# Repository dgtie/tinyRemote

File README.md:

# This project is obsolete
- please click [new tiny IR remote](https://github.com/dgtie/tinyRemote1/tree/main)

# tinyRemote
An infrared remote control with attiny414\
powered by 2 x AAA

## Keys
```
              ____
vol- (99)    |o  o| ch-  (77)
vol+ (32)    |o  o| ch+  (31)
shift(power) |o  o| input(mute)
             |____|
              UUUU

Hit SHIFT and indicator will turn on. Then hit a button while indicator is on.

It shall work for SHARP, LG and TOSHIBA.
It shall also work for SONY, PHILIPS and SAMSUNG. (but not yet verified)
```
## Connecting to PC

```
              ____
             |o  o| GND
      [UART] |o  o| 3V3
         GND |o  o| [UPDI]
         3V3 |____|
              UUUU
```
Connect tinyRemote to PC using a USB2TTL module via UPDI port or UART port. UPDI port is for programming attiny414. I am using [pyupdi](https://github.com/mraardvark/pyupdi).\
UART port is used for reading infrared code. There is an infrared transistor near the LED indicator. Point your remote controller CLOSE to it. To enter reading mode:
1. remove batteries
2. power up tinyRemote via UART port
3. IF SUCCESS, indicator will turn on. (It is a minor bug! Upon startup, Rx pin is checked. If it is high, enter reading mode.)

Baud rate is 115200. PC will receive BINARIES from tinyRemote representing the durations of marks and spaces. ZERO means break. The timing unit is 4.8 us.\
b2str.cpp is to convert the binaries to readable text string. The output will be durations in us.\
Decoding is done by PC (decode.cpp)\
pronto.cpp converts pronto hex to durations stream that to be decoded by decode.cpp
## Schematic

https://user-images.githubusercontent.com/42087847/192790861-0ea7e591-97eb-486d-b9d1-ebd6bcc5e6a8.mp4

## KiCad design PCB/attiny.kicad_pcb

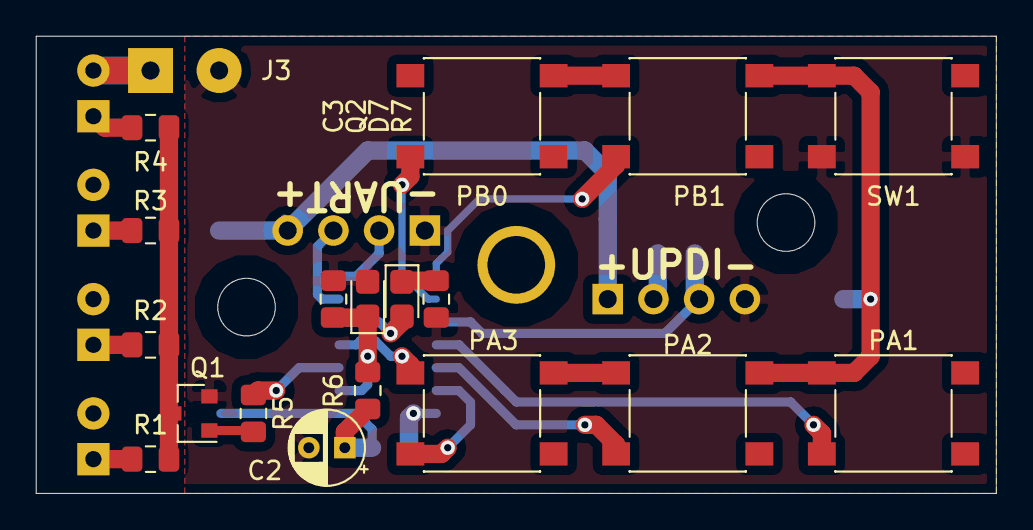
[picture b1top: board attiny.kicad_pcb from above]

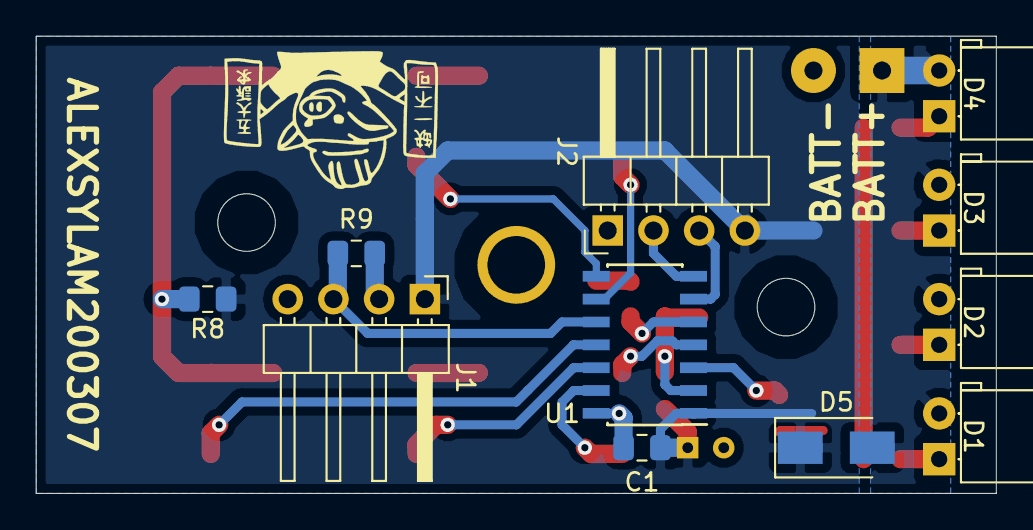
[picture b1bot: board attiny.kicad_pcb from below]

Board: 2 copper layers, 53.3 x 25.4 mm, 30 parts (11 on the bottom side), 23 nets.

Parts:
C1: 0u1; C_0805_2012Metric_Pad1.15x1.40mm_HandSolder
C2: 47u; CP_Radial_D4.0mm_P2.00mm
C3: 1n; C_0805_2012Metric_Pad1.15x1.40mm_HandSolder
D1, D2, D3, D4: LED; LED_D5.0mm_Horizontal_O1.27mm_Z3.0mm
D5: B120-E3; D_SMA
D7: LED; LED_0805_2012Metric_Castellated
J1, J2: Conn_01x04; PinHeader_1x04_P2.54mm_Horizontal
J3: Conn_01x02; SolderWirePad_1x02_P3.81mm_Drill1mm
PA1, PA2, PA3: SW_SPST; SW_SPST_PTS645
PB0, PB1: SW_SPST; SW_SPST_PTS645
Q1: BC817; SOT-23
Q2: Q_Photo_NPN; LED_0805_2012Metric_Castellated
R1, R2, R3, R4: 18; R_0805_2012Metric_Pad1.15x1.40mm_HandSolder
R5, R6, R8, R9: 4K7; R_0805_2012Metric_Pad1.15x1.40mm_HandSolder
R7: 330; R_0805_2012Metric_Pad1.15x1.40mm_HandSolder
SW1: SW_SPST; SW_SPST_PTS645
U1: ATtiny814-SS; SOIC-14_3.9x8.7mm_P1.27mm

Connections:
+BATT: D1.2, D2.2, D3.2, D4.2, D5.2, J3.1
GND: C1.2, C2.2, C3.2, J1.4, J2.1, J3.2, Q1.2, Q2.2, R7.2, SW1.2, U1.14
unnamed: C3.1, Q2.1, R6.2, U1.2
unnamed: D1.1, R1.1
unnamed: D2.1, R2.1
unnamed: D3.1, R3.1
unnamed: D4.1, R4.1
unnamed: D7.1, R7.1
unnamed: D7.2, U1.5
unnamed: J1.2, R9.1
unnamed: J1.3, R9.2, U1.10
unnamed: J2.2, U1.7
unnamed: J2.3, U1.6
unnamed: PA1.1, PA2.1, PA3.1, PB0.1, PB1.1, R8.2, SW1.1, U1.4
unnamed: PA1.2, U1.11
unnamed: PA2.2, U1.12
unnamed: PA3.2, U1.13
unnamed: PB0.2, U1.9
unnamed: PB1.2, U1.8
unnamed: Q1.1, R5.2
unnamed: Q1.3, R1.2, R2.2, R3.2, R4.2
unnamed: R5.1, U1.3
VCC: C1.1, C2.1, D5.1, J1.1, J2.4, R6.1, R8.1, U1.1

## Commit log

2020-03-15 Create temp
2020-03-30 Add files via upload
    add philips rc5
2020-04-10 add SHIFT timeout
2020-04-25 add logo 5dn1L
2023-04-11 obsolete project
